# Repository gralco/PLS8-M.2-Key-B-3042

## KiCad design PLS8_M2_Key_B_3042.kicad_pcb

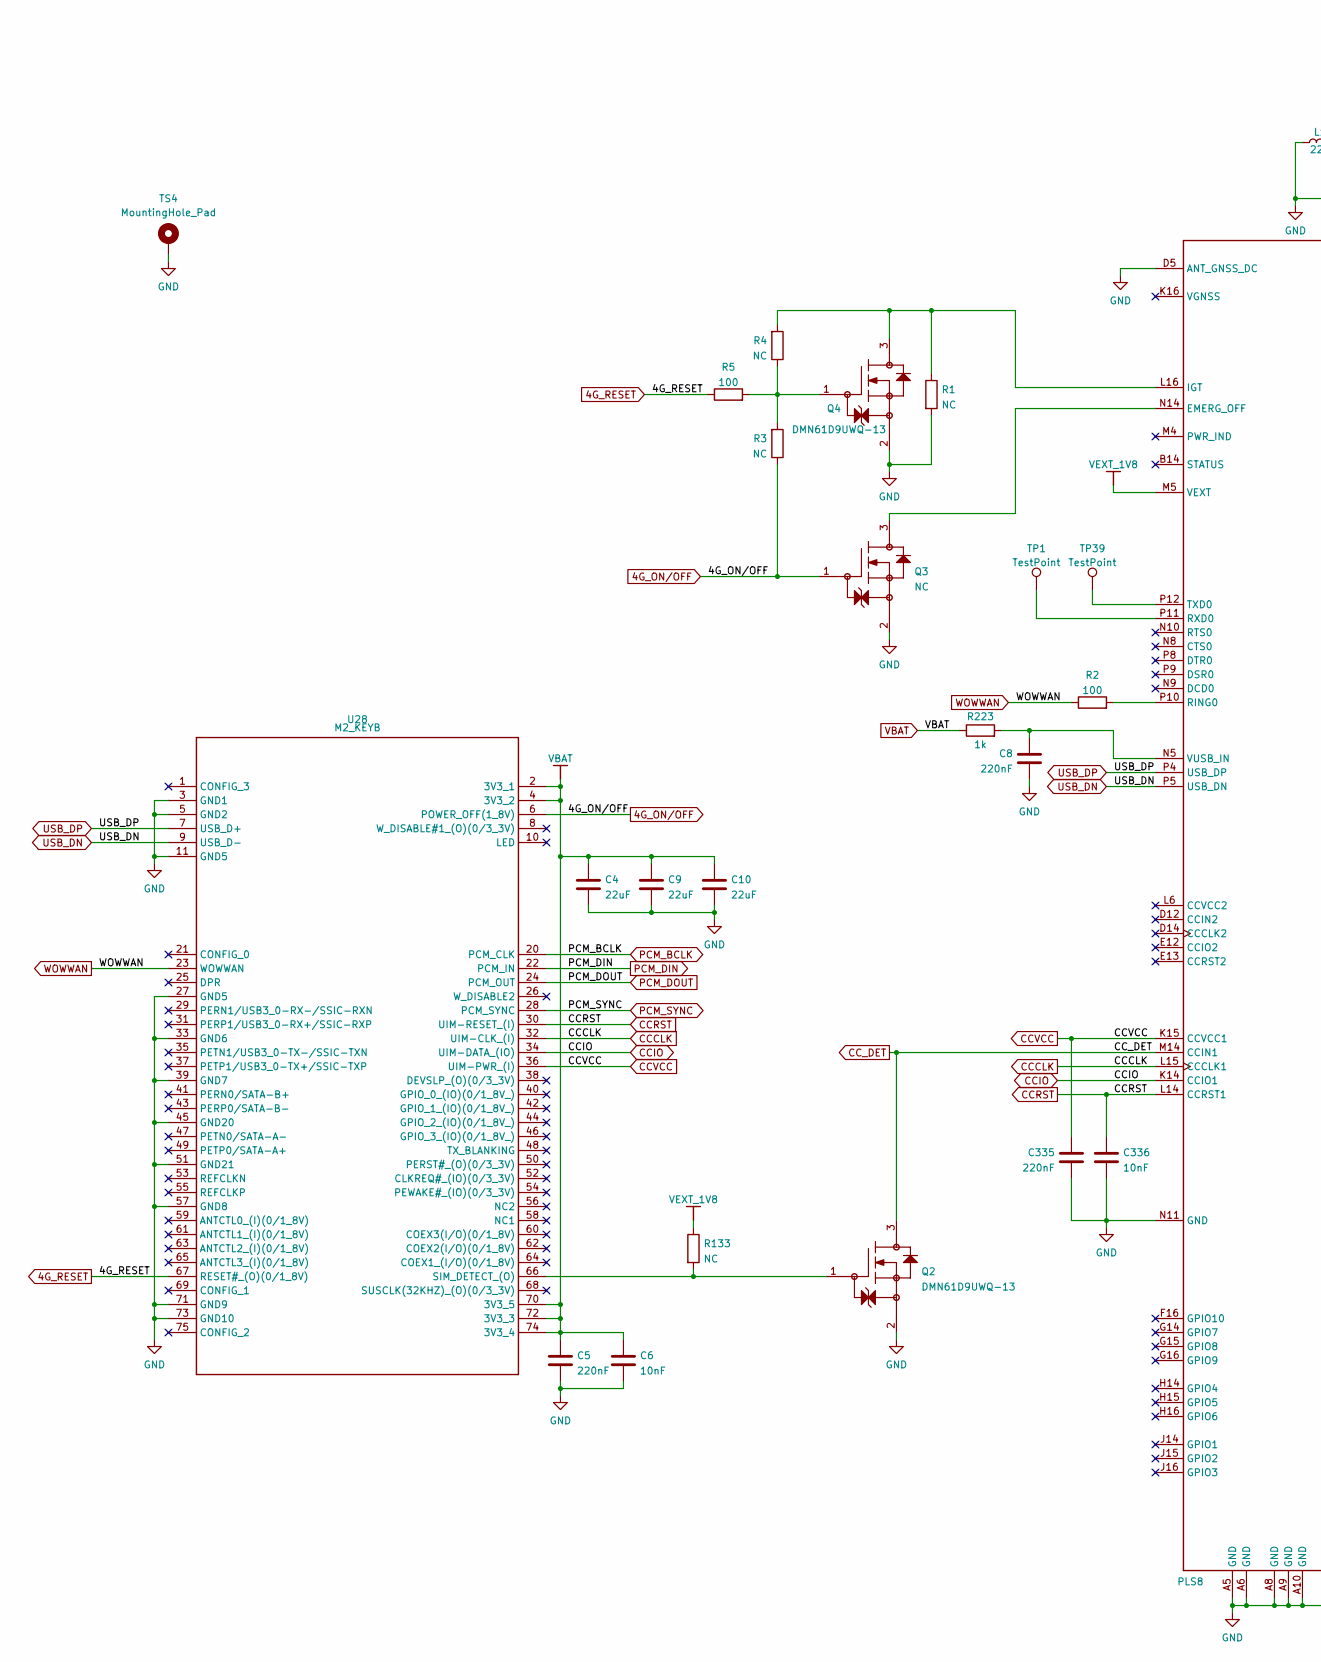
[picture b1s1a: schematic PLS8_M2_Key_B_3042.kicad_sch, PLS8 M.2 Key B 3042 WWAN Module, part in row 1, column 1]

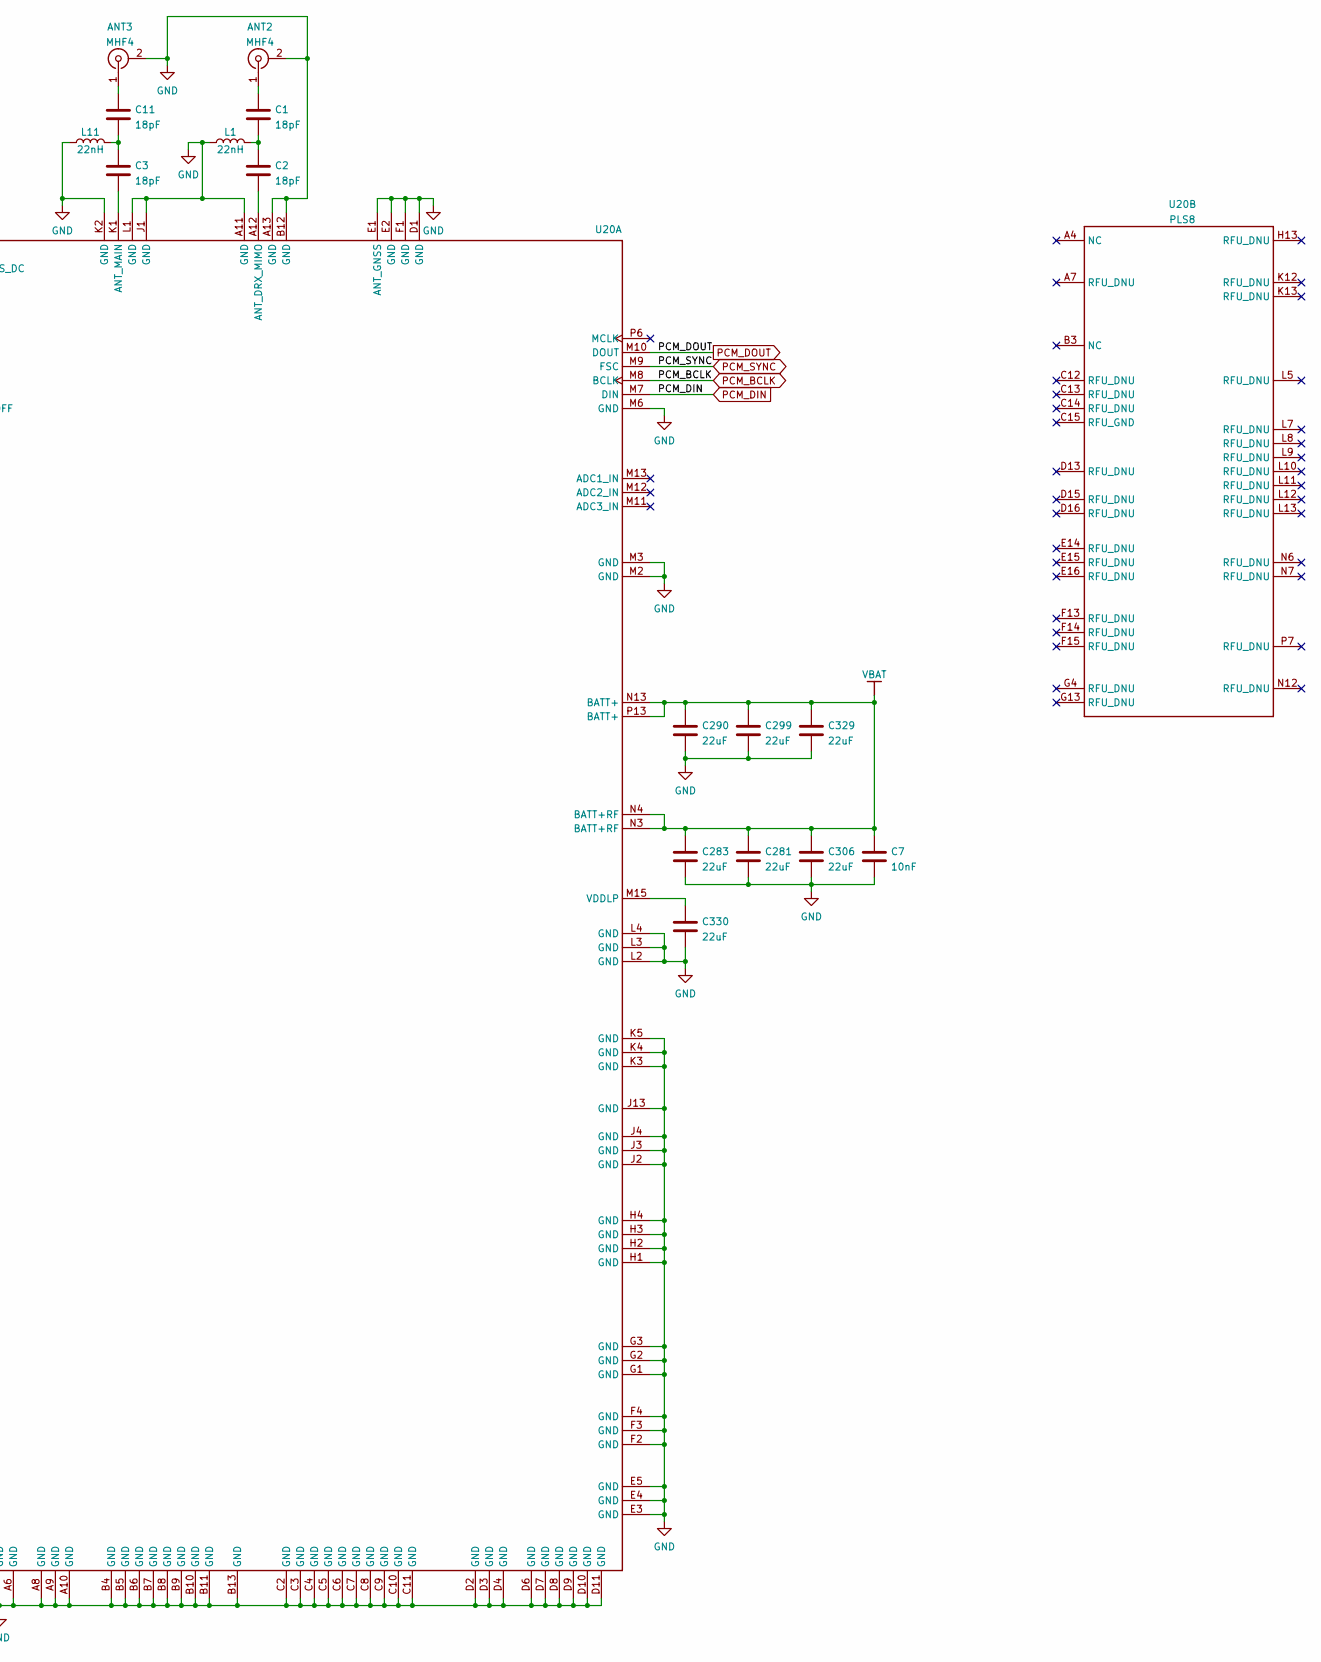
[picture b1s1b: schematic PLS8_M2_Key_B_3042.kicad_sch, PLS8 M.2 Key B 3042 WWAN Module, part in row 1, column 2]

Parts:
ANT2, ANT3: MHF4; MHF4_20449-001E; MFG Part Num RECE-20449-001E-01
C1, C2, C3, C11: 18pF; C_0402_1005Metric; Tolerance 5%; MFG Part Num 0402N180J250CT
C4, C9, C10, C281, C283, C290, C299, C306, C329, C330: 22uF; C_0603_1608Metric; Tolerance 20%; MFG Part Num CL10A226MP8NUNE
C5, C8, C335: 220nF; C_0402_1005Metric; Tolerance 10%; MFG Part Num UMK105B7222KV-F
C6, C7, C336: 10nF; C_0402_1005Metric; Tolerance 10%; MFG Part Num CL05B103KB5NNNC
L1, L11: 22nH; L_0402_1005Metric; Tolerance 5%; MFG Part Num LQW15AN22NJ8ZD
Q2, Q4: DMN61D9UWQ-13; SOT-323_SC-70; MFG Part Num DMN61D9UWQ-13
Q3: NC; SOT-323_SC-70; MFG Part Num DMN61D9UWQ-13
R1, R3, R4: NC; R_0402_1005Metric; Tolerance 1%; MFG Part Num RC0402FR-07100RL
R2, R5: 100; R_0402_1005Metric; Tolerance 1%; MFG Part Num RC0402FR-07100RL
R133: NC; R_0402_1005Metric; Tolerance 1%; MFG Part Num RC0402FR-0747RL
R223: 1k; R_0402_1005Metric; Tolerance 1%; MFG Part Num RMCF0402FT1K00
TP1, TP39: TestPoint; TEST_POINT
TS4: MountingHole_Pad; M.2_Mounting_Hole
U20: PLS8; MFG Part Num PLS8-US Rel.4
U28: M2_KEYB; M2_KEYB_3042

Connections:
4G_ON/OFF: Q3.1 (GATE), R3.1, U28.6 (POWER_OFF(1_8V))
4G_RESET: R5.1, U28.67 (RESET#_(O)(0/1_8V))
CCCLK: U20.L15 (CCCLK1), U28.32 (UIM-CLK_(I))
CCIO: U20.K14 (CCIO1), U28.34 (UIM-DATA_(IO))
CCRST: C336.1, U20.L14 (CCRST1), U28.30 (UIM-RESET_(I))
CCVCC: C335.2, U20.K15 (CCVCC1), U28.36 (UIM-PWR_(I))
CC_DET: Q2.3 (S), U20.M14 (CCIN1)
GND: ANT2.2 (Ext), ANT3.2 (Ext), C4.2, C5.2, C6.2, C7.2, C8.2, C9.2, C10.2, C281.2, C283.2, C290.2, C299.2, C306.2, C329.2, C330.2, C335.1, C336.2, L1.1, L11.1, Q2.2 (D), Q3.2 (D), Q4.2 (D), R1.2, TS4.1, U20.A5 (GND), U20.A6 (GND), U20.A8 (GND), U20.A9 (GND), U20.A10 (GND), U20.A11 (GND), U20.A13 (GND), U20.B4 (GND), U20.B5 (GND), U20.B6 (GND), U20.B7 (GND), U20.B8 (GND), U20.B9 (GND), U20.B10 (GND), U20.B11 (GND), U20.B12 (GND), U20.B13 (GND), U20.C2 (GND), U20.C3 (GND), U20.C4 (GND), U20.C5 (GND), U20.C6 (GND), U20.C7 (GND), U20.C8 (GND), U20.C9 (GND), U20.C10 (GND), U20.C11 (GND), U20.D1 (GND), U20.D2 (GND), U20.D3 (GND), U20.D4 (GND), U20.D5 (ANT_GNSS_DC), U20.D6 (GND), U20.D7 (GND), U20.D8 (GND), U20.D9 (GND), U20.D10 (GND), U20.D11 (GND), U20.E1 (ANT_GNSS), U20.E2 (GND), U20.E3 (GND), U20.E4 (GND), U20.E5 (GND), U20.F1 (GND), U20.F2 (GND), U20.F3 (GND), U20.F4 (GND), U20.G1 (GND), U20.G2 (GND), U20.G3 (GND), U20.H1 (GND), U20.H2 (GND), U20.H3 (GND), U20.H4 (GND), U20.J1 (GND), U20.J2 (GND), U20.J3 (GND), U20.J4 (GND), U20.J13 (GND), U20.K2 (GND), U20.K3 (GND), U20.K4 (GND), U20.K5 (GND), U20.L1 (GND), U20.L2 (GND), U20.L3 (GND), U20.L4 (GND), U20.M2 (GND), U20.M3 (GND), U20.M6 (GND), U20.N11 (GND), U28.3 (GND1), U28.5 (GND2), U28.11 (GND5), U28.27 (GND5), U28.33 (GND6), U28.39 (GND7), U28.45 (GND20), U28.51 (GND21), U28.57 (GND8), U28.71 (GND9), U28.73 (GND10)
unnamed: ANT2.1 (In), C1.1
unnamed: ANT3.1 (In), C11.1
unnamed: C1.2, C2.1, L1.2
unnamed: C2.2, U20.A12 (ANT_DRX_MIMO)
unnamed: C3.2, U20.K1 (ANT_MAIN)
unnamed: C8.1, R223.2, U20.N5 (VUSB_IN)
unnamed: C3.1, C11.2, L11.2
unnamed: C330.1, U20.M15 (VDDLP)
unnamed: Q2.1 (GATE), R133.2, U28.66 (SIM_DETECT_(O))
unnamed: Q3.3 (S), U20.N14 (EMERG_OFF)
unnamed: Q4.1 (GATE), R3.2, R4.1, R5.2
unnamed: Q4.3 (S), R1.1, R4.2, U20.L16 (IGT)
unnamed: R2.2, U20.P10 (RING0)
unnamed: TP1.1, U20.P11 (RXD0)
unnamed: TP39.1, U20.P12 (TXD0)
PCM_BCLK: U20.M8 (BCLK), U28.20 (PCM_CLK)
PCM_DIN: U20.M7 (DIN), U28.22 (PCM_IN)
PCM_DOUT: U20.M10 (DOUT), U28.24 (PCM_OUT)
PCM_SYNC: U20.M9 (FSC), U28.28 (PCM_SYNC)
USB_DN: U20.P5 (USB_DN), U28.9 (USB_D-)
USB_DP: U20.P4 (USB_DP), U28.7 (USB_D+)
VBAT: C4.1, C5.1, C6.1, C7.1, C9.1, C10.1, C281.1, C283.1, C290.1, C299.1, C306.1, C329.1, R223.1, U20.N3 (BATT+RF), U20.N4 (BATT+RF), U20.N13 (BATT+), U20.P13 (BATT+), U28.2 (3V3_1), U28.4 (3V3_2), U28.70 (3V3_5), U28.72 (3V3_3), U28.74 (3V3_4)
VEXT_1V8: R133.1, U20.M5 (VEXT)
WOWWAN: R2.1, U28.23 (WOWWAN)

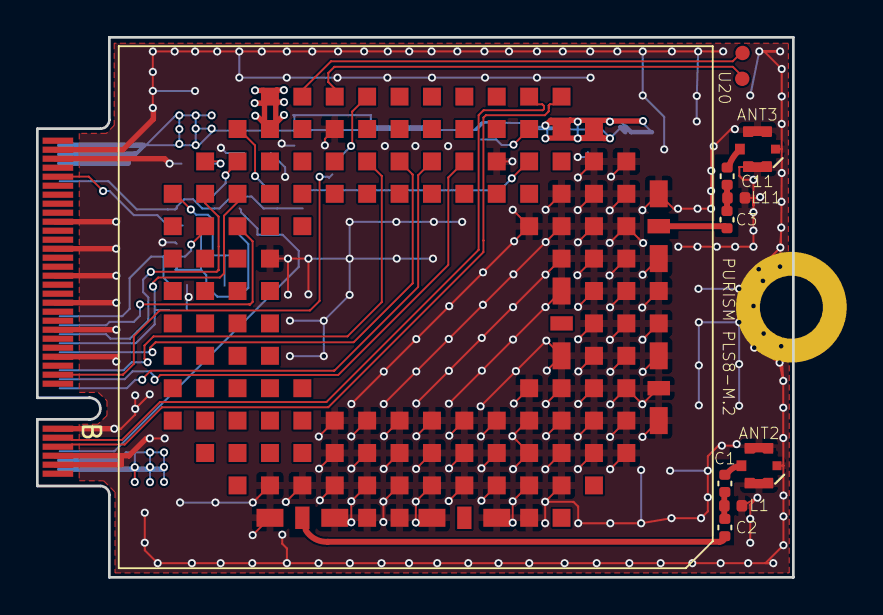
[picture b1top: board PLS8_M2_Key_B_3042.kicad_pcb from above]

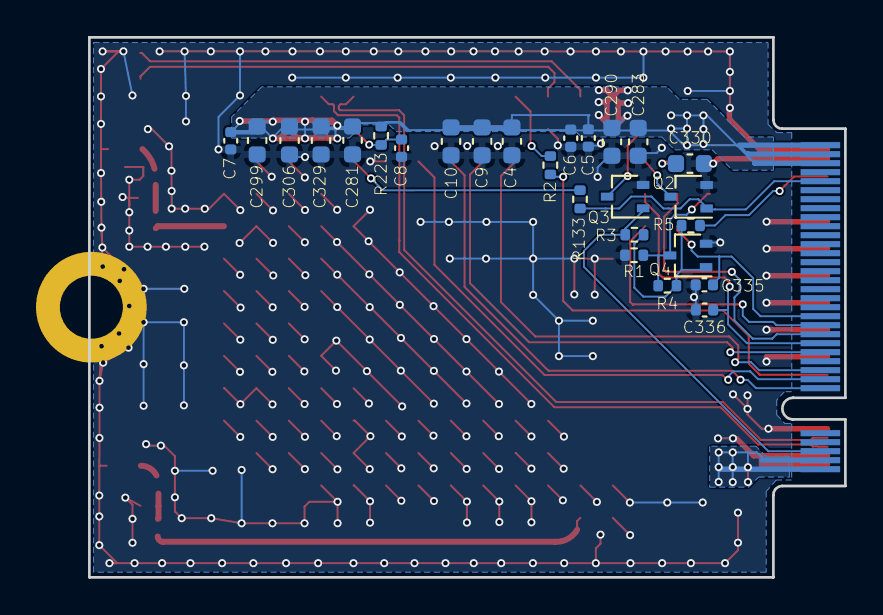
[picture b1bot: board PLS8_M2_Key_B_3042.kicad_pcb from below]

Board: 4 copper layers, 42.0 x 30.0 mm, 39 parts (26 on the bottom side), 32 nets.

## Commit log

2021-11-24 Add all of the imported files
2022-02-04 Use KiCad's built-in library for various symbols and footprints
    Make general improvements to the legibility of the schematic.
    Reuse some of the footprints from the dvk-mx8m-bsb project and others.
    Redefine all pins which were left as "passive" to being their
    corresponding functional definition.
    Make sure the schematic is passing ERC (no errors or warnings).
2022-02-04 Update the footprints in the layout using the ones assigned in the previous commit
    Make C7 10nF as it was previously.
    Fix the copper pour settings to make sure all connections are properly
    made.
    Adjust ATN2 and ANT3's footprint to have an underlying pad which copper
    pour can connect to.
2022-02-07 Fix all of the DRC violations.
    Made exceptions for courtyard overlaps where the components have not
    moved. Some components have been moved slightly to accomidate a minimum
    5mil soldermask sliver (especially due to the slightly larger pad sizes
    given in KiCad's footprint library).
    All silkscreen related-warnings have been ignored. The silkscreen
    reference designator text still needs to be moved.
2022-02-09 Fix up the silkscreen and use a board stackup that has a thickness of 0.8mm
2024-05-11 Add GPLv3+ license

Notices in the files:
PLS8_M2_Key_B_3042.kicad_sch:
Copyright 2022 GNU GPLv3+
